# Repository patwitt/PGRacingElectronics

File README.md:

<!-- [![Contributors][contributors-shield]][contributors-url] -->
<div id="top"></div>

<!-- PROJECT LOGO -->
<br />
<div align="center">

<h3 align="center">PGRacing Team Electronics</h3>
  
  <p align="center">
    Main repository for PGRacing Team Electronics group.
  </p>
</div>

## Structure
Each Project should have following folder structure:
- Project name
  - code - Container for source code (if any).
  - PCB - Container for KiCAD PCB project (if any).
  - Resources - Container for all additional resources.
  - Models - Container for all models (if any).

<!-- TABLE OF CONTENTS -->
<details>
  <summary>Projects</summary>
  <ol>
    <li><a href="#GearControl">Gear Control</a></li>
    <li><a href="#Dashboard">Dashboard</a></li>
    <li><a href="#PDM">Power Distribution Module</a></li>
    <li><a href="#ETC">Electronic Throttle Control</a></li>
  </ol>
</details>

## Getting started

This is an example of how you may give instructions on setting up your project locally.
To get a local copy up and running follow these simple example steps.

### Prerequisites

This is an example of how to list things you need to use the software and how to install them.
* example
  ```sh
  example install
  ```

### Installation

1. Clone the repo
   ```sh
   git clone https://github.com/patwitt/PGRacingElectronics.git
   ```
<p align="right">(<a href="#top">back to top</a>)</p>

## How to make changes
If you want to work on any project, follow this steps:
1. Fork the Project
2. Create your Feature Branch (`git checkout -b feature/AmazingFeature`)
3. Commit your Changes (`git commit -m 'Add some AmazingFeature'`)
4. Push to the Branch (`git push origin feature/AmazingFeature`)
5. Open a Pull Request

<!-- Gear Control Project -->
## GearControl
About gear control
<p align="right">(<a href="#top">back to top</a>)</p>

<!-- Dashboard Project -->
## Dashboard
About Dashboard
<p align="right">(<a href="#top">back to top</a>)</p>

<!-- Dashboard Project -->
## PDM
About PDM
<p align="right">(<a href="#top">back to top</a>)</p>

<!-- Dashboard Project -->
## ETC
About ETC
<p align="right">(<a href="#top">back to top</a>)</p>

[contributors-shield]: https://img.shields.io/github/contributors/patwitt/PGRacingElectronics.svg?style=for-the-badge
[contributors-url]: https://github.com/patwitt/PGRacingElectronics/graphs/contributors

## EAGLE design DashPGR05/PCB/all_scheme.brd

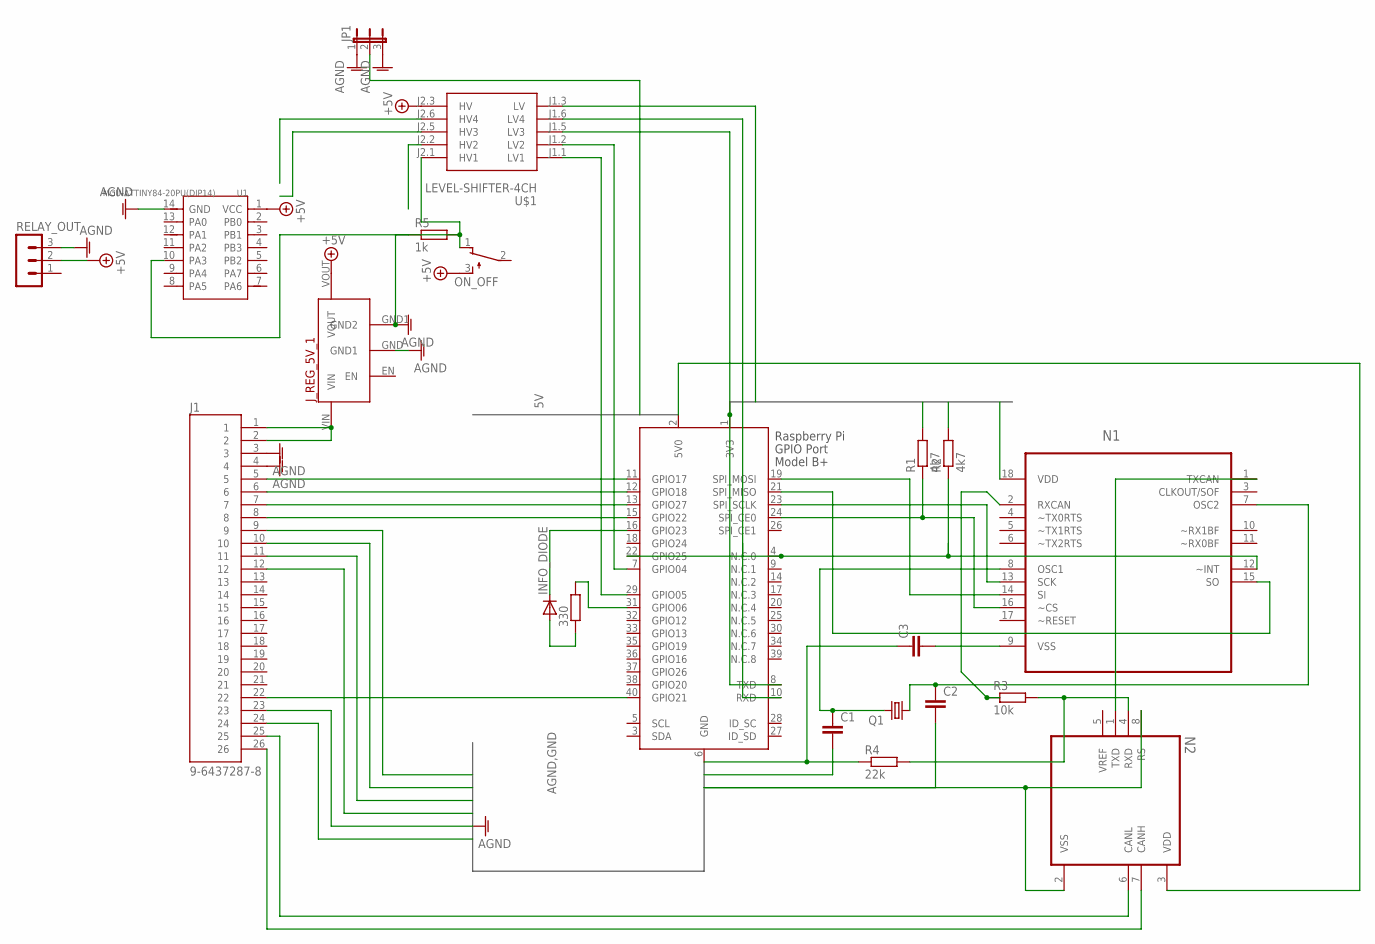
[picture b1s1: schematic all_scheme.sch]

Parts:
330: R0207/10; 0207/10
C1, C2, C3: C5/2.5; C5B2.5
INFO_DIODE: 1N4004; DO41-10
J1: 9-6437287-8; TE_9-6437287-8
JP1: JP2E; JP2
J_REG_5V_1: 5V_VOLTAGE_REGULATOR
N1: MCP2515-E/P; DIP254P762X432-18
N2: MCP2551-E/P; DIP787W46P254L927H533Q8
ON_OFF: TL32PO; TL3XPO
Q1: CRYSTALHC49S; HC49/S
R1, R2: 4k7; 0207/10
R3: 10k; 0207/10
R4: 22k; 0207/10
R5: 1k; 0204/7
RELAY_OUT: MA03-1
U1: MCU-ATTINY84-20PU(DIP14); DIP14-2.54-17.24X6.35MM
U$1: LEVEL-SHIFTER-4CH
X1: RASPI_GPIO_B+_PIN

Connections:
4K: N1.14 (SI), X1.19 (SPI_MOSI)
5V: JP1.2, N2.3 (VDD), X1.2 (5V0)
+5V: J_REG_5V_1.VOUT, ON_OFF.3 (S), RELAY_OUT.2, U1.1 (VCC), U$1.J2.3 (HV)
AGND: J1.3, J1.4, J1.23, JP1.1, JP1.3, J_REG_5V_1.GND (GND1), J_REG_5V_1.GND1 (GND2), R5.1, RELAY_OUT.3, U1.14 (GND)
B$1: N1.18 (VDD), R1.2, R2.2, U$1.J1.3 (LV)
GND: C1.2, C2.2, C3.1, J1.9, J1.10, J1.11, J1.12, J1.24, N2.2 (VSS), N2.8 (RS), R4.1, X1.6 (GND)
unnamed: J1.26, N2.7 (CANH)
unnamed: J1.25, N2.6 (CANL)
unnamed: J1.1, J1.2, J_REG_5V_1.VIN
unnamed: N1.13 (SCK), X1.23 (SPI_SCLK)
unnamed: N2.4 (RXD), R3.2, R4.2
unnamed: N1.15 (SO), X1.21 (SPI_MISO)
unnamed: N1.16 (~CS), R1.1, X1.24 (SPI_CE0)
unnamed: N1.1 (TXCAN), N2.1 (TXD)
unnamed: C1.1, N1.8 (OSC1), Q1.2
unnamed: N1.2 (RXCAN), R3.1
unnamed: C2.1, N1.7 (OSC2), Q1.1
unnamed: C3.2, N1.9 (VSS)
unnamed: N1.12 (~INT), R2.1, X1.4 (N.C.0), X1.22 (GPIO25)
unnamed: J1.5, X1.11 (GPIO17)
unnamed: J1.6, X1.12 (GPIO18)
unnamed: J1.7, X1.13 (GPIO27)
unnamed: J1.8, X1.15 (GPIO22)
unnamed: J1.22, X1.40 (GPIO21)
unnamed: 330.1, INFO_DIODE.A
unnamed: 330.2, X1.31 (GPIO06)
unnamed: INFO_DIODE.C, X1.16 (GPIO23)
unnamed: ON_OFF.1 (O), R5.2, U1.10 (PA3), U$1.J2.1 (HV1)
unnamed: U$1.J1.6 (LV4), X1.10 (RXD)
unnamed: U$1.J1.5 (LV3), X1.1 (3V3), X1.8 (TXD)
unnamed: U$1.J1.1 (LV1), X1.29 (GPIO05)
unnamed: U$1.J1.2 (LV2), X1.7 (GPIO04)

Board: 2 copper layers, 21 parts (0 on the bottom side), 32 nets, no tracks yet.

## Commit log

2021-11-01 Initial commit for GearControl and PDM PCB's
2021-11-01 Initial ReadMe
2021-11-01 Initial empty project for Gear Control v2 on STM32F4
2021-11-03 Initial commit Dash PGR-05
2021-11-03 Initial commit Telemetry - added telem.py code for interpreting pixhawk specific data
2021-11-03 Added PGR05 Dash code - not sure if newest
2021-11-04 New radnom file
2021-11-11 Added main.c file
2021-11-14 Add KiCAD common libraries
2021-11-15 New Steering wheel scheme
2021-11-17 Add buck converter
2021-11-22 Add Steering wheel model for PGR-06
2021-11-29 update kicad libs
2021-12-29 Steering Wheel Update
2021-12-29 Steering Wheel Update (#5)
2021-12-29 Remove unnecessary files
2021-12-30 Dashboard merge
    * Initial commit
    * Add buck converter
    * Remove unnecessary files
2022-01-09 initial commit telemtry schematic
2022-01-09 initial commit telemtry schematic (#7)
2022-01-09 Update PDM PCB
2022-01-16 rm files
2022-01-18 Dashboard (#9)
2022-01-18 Add correct files
2022-02-19 Add project config
2022-02-20 Added new brd for steering wheel
2022-02-22 New brd for steering wheel
2022-02-22 AT25SF128A External Loader for STM32CubeProgrammer
2022-02-22 At25 sf128 a external loader (#13)
    * AT25SF128A External Loader for STM32CubeProgrammer
2022-02-22 New brd for steering wheel (#12)
2022-02-22 Initial config for Display
2022-02-22 ADD new pcb files
2022-02-22 working display
2022-02-23 New pcb board
2022-02-23 Add signal led
2022-03-01 Some stuff
2022-03-01 Flash config
2022-03-01 Fix write error
2022-03-01 Dashboard (#15)
    * Initial commit
    * Add buck converter
    * Remove unnecessary files
    * rm files
    * Add correct files
    * Add project config
2022-03-01 Required 3D models for steering wheel
2022-03-01 Display and CubeIde config for SteeringWheel
2022-03-01 SOIC12 footprint
2022-03-01 Symbols for SW
2022-03-01 Add gitignore
2022-03-01 Steering wheel3 (#17)
    * New brd for steering wheel
    * Required 3D models for steering wheel
    * Display and CubeIde config for SteeringWheel
    * SOIC12 footprint
    * Symbols for SW
2022-03-01 Add gitignore (#16)
2022-03-01 Add makefile for internal and external flash
2022-03-01 Add usb C to board
2022-03-03 Add reset and pd pin to esp
2022-03-03 Switch footprints of converter
2022-03-03 Add pins for esp
2022-03-14 telemetry code init
2022-03-14 telemetry code init (#19)
2022-03-16 Add LED Driver
2022-03-17 Add text to pcb
2022-03-20 init commit
2022-03-21 Telemetry PCB added
2022-03-31 mlx90640 init
2022-03-31 PCB v1.0 (#21)
    * Add usb C to board
    * Add reset and pd pin to esp
    * Switch footprints of converter
    * Add LED Driver
    * Add text to pcb
2022-03-31 New brd design & final scheme
2022-03-31 final scheme & 60%pcb
2022-04-05 almost finished - space for Bartek
2022-04-07 Telemetry back (#24)
    * init commit
    * New brd design & final scheme
    * final scheme & 60%pcb
    * almost finished - space for Bartek
2022-04-07 mlx90640
2022-04-07 dzialaj prosze
2022-04-07 dzialaj prosze (#25)
2022-04-27 pre_finnal
2022-04-29 telemetry_back_finnal
2022-04-30 kicad libs
2022-05-04 finnal
2022-05-05 Remove Dashboard files from this branch
    This reverts commit ffcd00ee911598f18239aabaf1713ea3aea0f91a.
2022-05-05 Telemetry back v1.0 (#27)
    * init commit
    * New brd design & final scheme
    * final scheme & 60%pcb
    * almost finished - space for Bartek
    * pre_finnal
    * pre_finnal
2022-05-09 Remove PDM files
2022-05-09 Telemetry PCB added (#22)
    * Telemetry PCB added
    * Remove PDM files
2022-05-10 Add code for GearControl V1 (2021 working)
2022-05-10 Add PCB for PDM
2022-05-10 Add PCB for GearControl V1 (2021)
2022-05-10 Add missing files for GearControl V1
2022-05-15 Set settings for external flash and ram
2022-05-15 Increse flash clock
2022-05-25 Read data from ecumaster can to struct
2022-05-26 started code for telemtry saving
2022-05-26 add some files
2022-05-29 BSPD_PCB
2022-05-30 BSPD_PCB (#28)
2022-06-02 Telemetry_back v1.1
2022-06-02 almost done pcb (check communication with adc)
    almost done pcb (check communication with adc)
2022-06-04 BSPD
    With Gerbers
2022-06-13 Added MLX
2022-06-13 added missing files
2022-06-13 removed tracking files
2022-06-15 Fix ltdc and ram
2022-06-16 update gearcontrol v2
2022-06-18 latest updates for DBW controller and PID
2022-06-18 Add stm32f767 datasheets
2022-06-19 latest gear control updates
2022-06-20 Telemetry_back_v1.1
2022-06-20 Telemetry_back v1.1 (#31)
    * Telemetry_back v1.1
    * Telemetry_back_v1.1
    * Telemetry_back_v1.1
2022-06-27 Some code added
2022-06-27 added vss config + callback
2022-06-27 some name refactoring
2022-06-27 add old PDM
2022-06-29 GearControl v3 PCB
2022-07-07 even more code
2022-07-08 latest Gearcontrol V2 code
2022-07-08 remove old files
2022-07-08 update macro config
2022-07-08 remove .setting local
2022-07-11 Add Clutch Control from CAN. IMPORTANT - CHANGE CONFIG_ENABLE_CAN to TRUE after CAN is setup correctly in CubeMX!
2022-07-11 small servo update
2022-07-12 gear control updates
2022-07-24 New PCB for Dashboard
2022-07-26 some shit
2022-07-28 Some amazing features
2022-08-01 New updates on Gear Control
2022-08-01 fix servo range
2022-08-03 Steering Wheel update --working display + clutch paddle + can
2022-08-04 Fix gear state
2022-08-04 update gear states mapping
2022-08-04 fix request check
2022-08-04 update switch for requests
2022-08-05 update project config
2022-08-07 Test Setup
2022-08-07 Add stm32f767 datasheets (#30)
2022-08-07 Working display with can
    * Add makefile for internal and external flash
    * Add pins for esp
    * Set settings for external flash and ram
    * Increse flash clock
    * Read data from ecumaster can to struct
    * Fix ltdc and ram
2022-08-07 Gear control updates, clutch operations and injectors
2022-08-07 update Gear Control + add doxy
2022-08-07 Add new PCB for Dashboard (#34)
    * Add usb C to board
    * Add reset and pd pin to esp
    * Switch footprints of converter
    * Add LED Driver
    * Add text to pcb
    * New PCB for Dashboard
2022-08-07 update doxys
2022-08-07 update gear sensor adc
2022-08-07 small fixes
2022-08-08 fix PWM
2022-08-08 Telemetry_back_v2
2022-08-10 Gear control updates, add rev matching
2022-08-10 small updates
2022-08-11 Led and freertos code refactor
2022-08-12 update CAN
2022-08-13 Added Can + sending Ecumaster structure by rfd module
2022-08-15 GPS ang GYRO active, sending ecu data
2022-08-15 Gear requests fix and refactor, CAN config update
2022-08-16 Set oil, gear unkonwn alert
2022-08-16 fsg start
    can config modification
2022-08-18 Refactor led code
2022-08-19 Fix minor bugs
2022-08-24 Steering wheel status, calc fuel usage
2022-08-24 Changed ecu freq, added new can frame
2022-08-25 can id fix
    can msg id resloved by enum, default pwm changed
2022-08-26 gear control fixes
2022-08-26 reduce gear sens monitoring time. update init range condition
2022-08-27 alpe adria fixes
2022-08-27 add comments
2022-08-27 add injectors cut
2022-08-27 add timing stats to CAN msg
2022-08-28 Gear control fsg (#36)
    * fsg start
    can config modification
    * can id fix
    can msg id resloved by enum, default pwm changed
    * alpe adria fixes
    * updates
2022-08-28 refactor gear control
2022-09-13 Add more files do gitignore
2022-09-13 New project version
2022-09-13 Fix compile errors
2022-09-19 Telemetry_back
2022-09-25 Initial scheme
2022-09-25 Final schematic
2022-09-25 Minor changes, attached footprints
2022-09-28 update gitignore
2022-09-28 Setup adc with timer
2022-10-01 Add CAN communication initialization
2022-10-01 Telemetry (#35)
    * Telemetry_back v1.1
    * Telemetry_back_v1.1
    * Telemetry_back_v1.1
    * Telemetry_back_v2
    * Telemetry_back
2022-10-02 Setup freertos function for led bar
2022-10-05 .remove libraries and execs from gitignore
2022-10-05 Adc on timer, add Middleware files
2022-10-10 with vss and damper
2022-10-13 Code cleanup
2022-11-03 Fixed GPS, changed adc to use dma, change abs calcualtions
2022-11-03 Minor code refacoring
2022-11-04 STABLE fot tests 04.11
2022-11-04 NOT TESTED added sending data to module and sending can frames
2022-11-04 Quick Fix
2022-11-09 Version 09.11
    ABS new calculation, raw data CAN sending
2022-11-10 Changed abs calculation method
2023-05-20 DBW updates
2023-06-13 Latest updates for smaller Bosch Throttle Body
2023-07-08 Added safety system for DBW
2023-11-03 Version 1.0.0, active: GPS, IMU, 4xDamper, Steering Wheel, 2xABS
2024-02-04 Update GearCtrl PCB for safety system for ETB
2024-02-15 Added gitignore
2024-02-15 Test1
2024-03-21 Update code
2024-03-23 initial testing of new ETB
2024-05-27 add kalman, fix PID
2024-06-28 FIXES FOR NEW PCB!
2024-07-09 Flashed code
2024-07-10 Rules compliant DBW
2024-07-10 Update feasible range
2024-07-15 DBW refactor + rules fixes
2024-07-18 Further updates, Throttle Blip updates
2024-07-18 Reset safaty only on idle tps
2024-08-01 Update Pid params
2024-08-01 Update apps range, add gamma
2024-08-03 throttle blip
2024-08-03 Fixes for safety after refactor
2024-08-04 Add Marcin Throttle Blip
2025-05-04 gc as adc to can

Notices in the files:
parts and their libraries:
diy-modules: Released under the Creative Commons Attribution 4.0 International License: http://creativecommons.org/licenses/by/4.0
